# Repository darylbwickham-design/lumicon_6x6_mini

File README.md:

# Lumi-Con 6×6 Matrix Mini v1.1.0

A 36-key open-source stream controller with an integrated ST7735 TFT display, phone-first device setup, Lumia plugin support, and optional virtual pet features.

This project uses:

- a **Raspberry Pi Pico (RP2040)** to scan the 6×6 matrix
- an **ESP8266** to handle the TFT, Wi-Fi, HTTP API, and Lumia communication
- a **Lumia plugin** to receive key events, expose variables, and send display / pet actions back to the device

---

## What it does

### Inputs: device → Lumia

- The Pico scans all 36 keys and sends UART packets to the ESP8266.
- The ESP8266 converts those into Lumia-facing events:
  - **Short press:** `0–35`
  - **Long press:** `36–71` (`key + 36`)
- The ESP8266 posts events to the Lumia plugin listener.

### Display and pet control: Lumia → device

The ESP8266 exposes local HTTP endpoints so Lumia can send text, status updates, clear commands, health checks, and pet actions back to the device.

---

## Recommended current release set

Use this combination as the current baseline:

- **Pico firmware:** `6x6_test_pico.ino` or UF2 built from it
- **ESP firmware:** `lumicon_6x6_mini_v1_1_4.ino`
- **Lumia plugin:** `6x6_matrix_mini_v1_1_3.lumiaplugin`

### Plugin naming note

Older project history refers to the integrated plugin as **v5.2**. That package is effectively the **1.0.0** public baseline for the newer `6x6 matrix mini` plugin line.

If you are using the newer plugin packages, treat these as the current progression:

- `1.0.0` = old integrated `v5.2`
- `1.1.x` = newer `6x6 matrix mini` plugin line

---

## Main features

### Easy phone-based setup

On first boot, the ESP firmware can create a setup access point named **`Lumi-Con-Setup`**.

Use a mobile phone for first-time Wi-Fi setup, not the streaming PC or desktop browser. On your phone, connect to the setup Wi-Fi network, then tap the phone's Wi-Fi sign-in notification or open the phone's browser at:

`http://192.168.4.1`

From there you can join the device to your Wi-Fi network without editing the firmware source.

### Browser-based plugin host pairing

Once the device is already on your normal Wi-Fi network, you can set the Lumia/plugin host from any browser on the same network instead of recompiling the ESP sketch.

Use:

`http://<device-ip>/plugin?host=<pc-ip>`

This host is stored by the ESP and reused after reboot.

### TFT display actions

The Lumia plugin can send:

- **Display: Add Line**
- **Display: Set Status**
- **Display: Clear**

This is useful for:

- scene/status text
- alerts
- chat-style output
- debugging
- custom stream messages

### Virtual pet support

The platform includes an optional virtual pet system.

The current plugin supports these pet actions:

- `status`
- `sync`
- `feed`
- `play`
- `clean`
- `sleep`
- `med`
- `discipline`
- `reset`

The plugin also exposes pet variables for overlays, alerts, and automations.

### More reliable idle handling

The current plugin line performs a silent health check using `/status?silent=1` before marking the device offline, which helps avoid false disconnects when the device is simply idle.

### Multiple runtime modes

The current ESP firmware supports:

- **Chat mode**
- **noPet Debug mode**
- **Pet mode**
- **LCD Only Mode**

---

## Repository layout

At the time of writing, the public repository includes top-level folders for **3d files**, **Docs**, **Firmware**, and **Plugins/v5.2**. This README is written around the latest firmware and plugin files reviewed for this update, even where the live public repo still shows older packaging and README text. 

Recommended repo structure going forward:

- `Firmware/` for Pico and ESP firmware
- `Plugins/` for Lumia plugin packages and source
- `Docs/` for setup docs, changelogs, and release notes
- `3d files/` for enclosure and print assets

---

## Hardware overview

### Pico ↔ 6×6 matrix

The Pico scans the matrix.

Current Pico test firmware pin mapping:

#### Rows (inputs with pullups)
- `R0 -> GP12`
- `R1 -> GP1`
- `R2 -> GP2`
- `R3 -> GP3`
- `R4 -> GP4`
- `R5 -> GP5`

#### Columns (outputs)
- `C0 -> GP6`
- `C1 -> GP7`
- `C2 -> GP8`
- `C3 -> GP9`
- `C4 -> GP10`
- `C5 -> GP11`

### Pico → ESP8266 UART

- `Pico GP0 (TX) -> ESP RX / GPIO3`
- `Pico GND -> ESP GND`
- Optional: `1k` resistor in series on the TX line

### ESP8266 → ST7735 TFT (SPI)

Current ESP firmware pin mapping:

- `TFT VCC -> 3V3`
- `TFT GND -> GND`
- `TFT SCK -> D5 / GPIO14`
- `TFT MOSI -> D7 / GPIO13`
- `TFT CS -> D2 / GPIO4`
- `TFT DC -> D1 / GPIO5`
- `TFT RST -> ESP RST` recommended

### Important flashing note

Disconnect `Pico GP0 (TX) -> ESP RX (GPIO3)` while uploading firmware to the ESP8266.

---

## Arduino IDE setup

### 1) Install Arduino IDE

Download from:

`https://www.arduino.cc/en/software`

### 2) Add board manager URLs

In Arduino IDE, open:

`File -> Preferences -> Additional Boards Manager URLs`

Add:

#### ESP8266
`http://arduino.esp8266.com/stable/package_esp8266com_index.json`

#### Pico / RP2040 (Earle Philhower)
`https://github.com/earlephilhower/arduino-pico/releases/download/global/package_rp2040_index.json`

### 3) Install board packages

Open:

`Tools -> Board -> Boards Manager`

Install:

- **ESP8266 by ESP8266 Community**
- **Raspberry Pi Pico/RP2040 by Earle Philhower**

### 4) Install required libraries for the ESP8266 firmware

Install through **Sketch -> Include Library -> Manage Libraries**:

- **WiFiManager**
- **Adafruit GFX Library**
- **Adafruit ST7735 and ST7789 Library**

The Pico test firmware does not require extra third-party Arduino libraries beyond the RP2040 board package.

---

## Flashing the firmware

### 1) Flash the Pico

Flash your current Pico matrix-scanner firmware first.

If you use a UF2 build:

1. Hold **BOOTSEL** while plugging the Pico into USB
2. The Pico appears as a USB drive
3. Drag and drop the UF2 file

If you use source:

- Open `6x6_test_pico.ino`
- Select your Pico board
- Upload normally

### 2) Flash the ESP8266

1. Disconnect `Pico GP0 -> ESP RX`
2. Open `lumi_con_esp_integrated_0_4_2.ino`
3. Select the correct ESP8266 board
4. Upload the firmware
5. Reconnect `Pico GP0 -> ESP RX`

---

## First-time device setup

### Step 1: connect the ESP to Wi-Fi

1. Power the device
2. On your mobile phone, open Wi-Fi settings and connect to the access point:
   - **`Lumi-Con-Setup`**
3. Tap the phone's Wi-Fi sign-in notification. If it does not appear, open the phone's browser and go to:
   - **`http://192.168.4.1`**
4. Select your Wi-Fi network and enter the password
5. Save
6. The ESP reboots and the display shows its IP address

Use the phone for this captive-portal step. A desktop or streaming PC browser is more likely to stay on your normal network and miss the device setup page.

### Step 2: install and configure the Lumia plugin

Install the current Lumia plugin package.

Recommended current plugin:

- `6x6_matrix_mini_v1_1_3.lumiaplugin`

In Lumia plugin settings:

- **Enable Listener**: `ON`
- **Listen Port**: `8787`
- **Shared Secret**: blank unless you intentionally set one in firmware
- **ESP Base URL**: set this to your device address, for example:
  - `http://192.168.1.50`

Recommended defaults:

- **ESP UI Mode**: `legacy_get`
- **Status Path**: `/status`
- **Pet Path**: `/pet`

### Step 3: pair the device with the plugin host

After phone Wi-Fi setup is finished and the device shows its IP address, run this from a browser on the same network:

`http://<device-ip>/plugin?host=<pc-ip>`

Example:

`http://192.168.1.50/plugin?host=192.168.1.87`

This tells the ESP where the Lumia plugin listener is running.

### Step 4: confirm the device is responding

Useful test URLs:

- `http://<device-ip>/health`
- `http://<device-ip>/plugin`
- `http://<device-ip>/msg?t=Hello`
- `http://<device-ip>/status?t=OK`
- `http://<device-ip>/clear`
- `http://<device-ip>/pet?action=status`

---

## Current HTTP API

The current ESP firmware supports these user-facing routes:

- `GET /`
- `GET /msg?t=...`
- `GET /status?t=...`
- `GET /status?silent=1`
- `GET /clear`
- `POST /ui`
- `GET /health`
- `GET /plugin`
- `GET /plugin?host=<pc-ip>`
- `GET /plugin?clear=1`
- `GET /pet?action=status|sync|feed|play|clean|sleep|med|toggleSleep|discipline|reset`

---

## Boot behavior and modes

Current boot-key behavior in the ESP firmware:

- Hold **Pico key 0** at boot -> reset Wi-Fi settings and restart
- Hold **Pico key 1** at boot -> Chat mode
- Hold **Pico key 2** at boot -> noPet Debug mode
- Hold **Pico key 35** at boot -> Pet mode

Current runtime modes include:

- **Chat mode**
- **noPet Debug mode**
- **Pet mode**
- **LCD Only Mode**

---

## Lumia plugin: what it adds

### Alerts

The current plugin provides:

- **6x6 short**
- **6x6 long**
- **Pet**

### Actions

The current plugin provides:

- **Display: Add Line**
- **Display: Set Status**
- **Display: Clear**
- **Pet Action**

### Useful variables

The plugin exposes device and pet variables, including:

- `{{event}}`
- `{{kind}}`
- `{{key_label}}`
- `{{held_ms}}`
- `{{device_id}}`
- `{{device_ip}}`
- `{{device_rssi}}`
- `{{device_connected}}`
- `{{device_status_text}}`
- `{{pet_stage_name}}`
- `{{pet_hunger}}`
- `{{pet_happiness}}`
- `{{pet_health}}`
- `{{pet_poop}}`
- `{{pet_change_name}}`

---

## Quick usage ideas

- Use **Display: Set Status** for stream state text such as `LIVE`, `BRB`, or scene names.
- Use **Display: Add Line** for scrolling messages, redeems, or now-playing text.
- Use **Pet Action -> status** before updating a pet overlay.
- Use **Pet Action -> sync** after reconnecting the device.
- Use **Pet Action -> clean** when a pet event indicates poop-related state changed.

---

## Troubleshooting

### ESP upload fails

Disconnect `Pico GP0 (TX) -> ESP RX (GPIO3)` while flashing the ESP8266.

### The setup AP does not appear

- Reboot the device
- Use the factory reset boot key path if Wi-Fi credentials need clearing
- Make sure the ESP firmware actually flashed successfully

### TFT stays white or blank

- Check TFT power and SPI wiring
- Wire `TFT RST -> ESP RST`
- If colours are wrong, check the ST7735 tab/init settings in firmware

### Lumia receives nothing

- Make sure the plugin listener is enabled
- Confirm the plugin listen port is `8787` unless intentionally changed
- Confirm the ESP host pairing was set with:
  - `http://<device-ip>/plugin?host=<pc-ip>`
- Confirm the PC and device are on the same LAN

### Lumia can receive key events but cannot send text or pet commands

- Set **ESP Base URL** in plugin settings to the device address
- Check `/health` and `/status` in a browser on the same network after phone setup is complete
- Confirm the device IP did not change after a reboot

### The plugin looks “offline” after idle time

The current plugin line performs one silent health check first. If you still see offline behavior:

- confirm **ESP Base URL** is correct
- confirm **Status Path** is `/status`
- confirm the device responds to:
  - `http://<device-ip>/status?silent=1`

---

## Summary

**Lumi-Con 6×6 Matrix Mini is a 36-key open-source stream controller with an integrated TFT display, phone-first Wi-Fi setup, Lumia plugin support, virtual pet features, and flexible display/status workflows for streams and automations.**

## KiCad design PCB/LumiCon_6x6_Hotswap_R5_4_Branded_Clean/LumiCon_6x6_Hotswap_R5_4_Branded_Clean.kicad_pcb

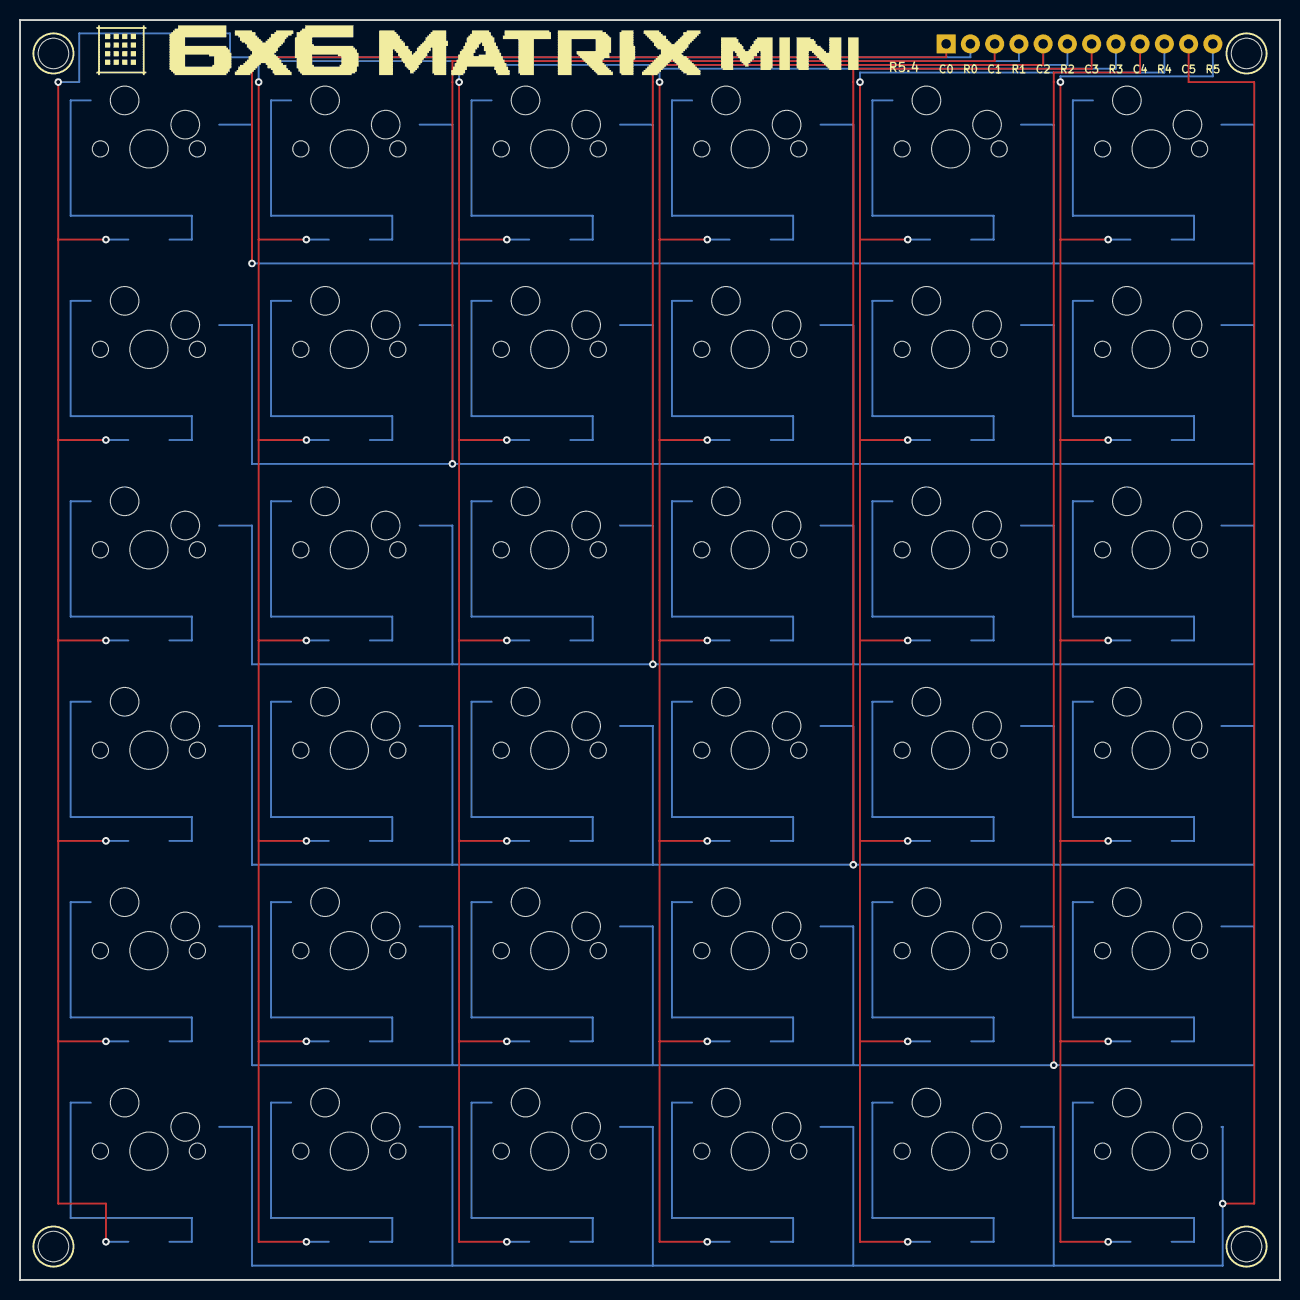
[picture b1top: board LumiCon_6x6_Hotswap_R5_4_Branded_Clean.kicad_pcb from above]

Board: 2 copper layers, 132.0 x 132.0 mm, 77 parts (0 on the bottom side), 48 nets.

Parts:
D1, D2, D3, D4, D5, D6, D7, D8, D9, D10, D11, D12, D13, D14, D15, D16, D17, D18, D19, D20, D21, D22, D23, D24, D25, D26, D27, D28, D29, D30, D31, D32, D33, D34, D35, D36: 1N4148W; D_SOD-123
H1, H2, H3, H4: MountingHole_3.2mm_M3
J1: MATRIX_1x12; PinHeader_1x12_P2.54mm
SW1, SW2, SW3, SW4, SW5, SW6, SW7, SW8, SW9, SW10, SW11, SW12, SW13, SW14, SW15, SW16, SW17, SW18, SW19, SW20, SW21, SW22, SW23, SW24, SW25, SW26, SW27, SW28, SW29, SW30, SW31, SW32, SW33, SW34, SW35, SW36: Kailh_CPG151101S11; SW_Hotswap_Kailh_1.00u

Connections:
COL0: J1.1, SW1.1, SW2.1, SW3.1, SW4.1, SW5.1, SW6.1
COL1: J1.3, SW7.1, SW8.1, SW9.1, SW10.1, SW11.1, SW12.1
COL2: J1.5, SW13.1, SW14.1, SW15.1, SW16.1, SW17.1, SW18.1
COL3: J1.7, SW19.1, SW20.1, SW21.1, SW22.1, SW23.1, SW24.1
COL4: J1.9, SW25.1, SW26.1, SW27.1, SW28.1, SW29.1, SW30.1
COL5: J1.11, SW31.1, SW32.1, SW33.1, SW34.1, SW35.1, SW36.1
K00_D: D1.1, SW1.2
K01_D: D7.1, SW7.2
K02_D: D13.1, SW13.2
K03_D: D19.1, SW19.2
K04_D: D25.1, SW25.2
K05_D: D31.1, SW31.2
K10_D: D2.1, SW2.2
K11_D: D8.1, SW8.2
K12_D: D14.1, SW14.2
K13_D: D20.1, SW20.2
K14_D: D26.1, SW26.2
K15_D: D32.1, SW32.2
K20_D: D3.1, SW3.2
K21_D: D9.1, SW9.2
K22_D: D15.1, SW15.2
K23_D: D21.1, SW21.2
K24_D: D27.1, SW27.2
K25_D: D33.1, SW33.2
K30_D: D4.1, SW4.2
K31_D: D10.1, SW10.2
K32_D: D16.1, SW16.2
K33_D: D22.1, SW22.2
K34_D: D28.1, SW28.2
K35_D: D34.1, SW34.2
K40_D: D5.1, SW5.2
K41_D: D11.1, SW11.2
K42_D: D17.1, SW17.2
K43_D: D23.1, SW23.2
K44_D: D29.1, SW29.2
K45_D: D35.1, SW35.2
K50_D: D6.1, SW6.2
K51_D: D12.1, SW12.2
K52_D: D18.1, SW18.2
K53_D: D24.1, SW24.2
K54_D: D30.1, SW30.2
K55_D: D36.1, SW36.2
ROW0: D1.2, D7.2, D13.2, D19.2, D25.2, D31.2, J1.2
ROW1: D2.2, D8.2, D14.2, D20.2, D26.2, D32.2, J1.4
ROW2: D3.2, D9.2, D15.2, D21.2, D27.2, D33.2, J1.6
ROW3: D4.2, D10.2, D16.2, D22.2, D28.2, D34.2, J1.8
ROW4: D5.2, D11.2, D17.2, D23.2, D29.2, D35.2, J1.10
ROW5: D6.2, D12.2, D18.2, D24.2, D30.2, D36.2, J1.12

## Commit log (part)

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2026-03-27 Delete Docs/Schematic.pdf
    wiring was backwards for key matrix
2026-03-27 Update README.md
    partial update
2026-04-06 Update release notes
